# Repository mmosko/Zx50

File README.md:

# Zx50 Distributed Computer

> **A retro-modern, modular computing platform built around the Zilog Z80 microprocessor — featuring paged virtual
memory, high-speed Shadow DMA, and FPGA coprocessing.**

---

## 1. Welcome to the Zx50

The **Zx50** is a custom, modular computing architecture that marries the classic 8-bit computing ethos of the
late-1970s and 1980s with modern high-speed digital engineering.

At the heart of the system is the **Zilog Z80** microprocessor (inducted into
the [IEEE Spectrum Chip Hall of Fame](https://spectrum.ieee.org/chip-hall-of-fame-zilog-z80-microprocessor),
see the official [Zilog Z80 Datasheet](https://www.zilog.com/docs/z80/um0080.pdf)). 
The Zx50 reimagines the Z80 as a modern distributed computing workstation.

### What makes the Zx50 "Retro-Modern"?

* **Bare-Metal Simplicity**: The CPU executes pure, unadulterated Z80 machine code. You can program it in assembly, C,
  or native BASIC just like classic machines.
* **Breaking the 64KB Limit**: A custom hardware Memory Management Unit (MMU) implemented in a CPLD provides 4KB paged
  virtual memory across 1MB+ of physical SRAM.
* **Dual-Bus Highway**: In addition to the standard Z80 bus, a dedicated **40 MHz Shadow DMA Bus** streams data (network
  packets, disk blocks, and peer-to-peer memory transfers) in the background without halting the Z80.
* **Hardware Acceleration**: A modern FPGA coprocessor offloads 32-bit and 64-bit floating-point math, emulating the
  vintage AMD Am9511 APU with single-cycle lookups.
* **Deep Visibility**: Built-in microcontroller instrumentation (RP2040 and Microchip PIC) allows real-time bus
  snooping, cycle-by-cycle single stepping, and telemetry via an active front panel and bus probe.

---

## 2. Core Silicon & Chip Manifest

The Zx50 blends period-accurate Zilog NMOS/CMOS silicon with modern programmable logic and companion microcontrollers:

| Chip / Component              | Technology          | Primary Role in Zx50                                                                                                                               |
|:------------------------------|:--------------------|:---------------------------------------------------------------------------------------------------------------------------------------------------|
| **Zilog Z84C0020**            | CMOS CPU            | **Central Processor**: Runs at 8 MHz – 10 MHz with 16-bit addressing and an 8-bit data path.                                                       |
| **Zilog Z84C30**              | CMOS CTC            | **Counter/Timer Circuit**: 4 independent channels generating periodic system ticks and baud rate clocks.                                           |
| **Zilog Z84C40**              | CMOS DART/SIO       | **Dual Serial Controller**: Dual-channel serial communications (Port 0 for USB console, Port 1 for RS-232) supporting IM 2 vectored interrupts.    |
| **Microchip ATF1508**         | 5V CPLD             | **Memory Controller & MMU**: Address Translation Latch (ATL) mapping 64KB logical address space into 16 independent 4KB pages backed by 1MB+ SRAM. |
| **Lattice MachXO2 / MachXO3** | Flash FPGA          | **Math Coprocessor & SmartNIC**: 32-bit/64-bit floating point APU emulation, fast BRAM LUT math, and future LVDS RDMA distributed clustering.      |
| **WIZnet W5300**              | Hardwired TCP/IP    | **10/100 Ethernet Controller**: Memory-mapped window for wire-speed network packet streaming via Z80 `LDIR`/`LDDR` block transfers.                |
| **WCH CH376S**                | Mass Storage IC     | **USB Host & SD Card Controller**: Hardware FAT16/FAT32 file manager mapped into the Z80 I/O space.                                                |
| **Raspberry Pi RP2040**       | Dual ARM Cortex-M0+ | **Instrumentation & Display**: Drives the Front Panel display/switches and coordinates circular trace buffers on the Bus Probe.                    |
| **Microchip PIC18F4620**      | 8-bit MCU           | **Real-Time Bus Interface**: Works alongside the RP2040 on the Bus Probe for cycle sampling, pin toggling, and non-intrusive bus analysis.         |

---

## 3. System Topology & Card Placement

The Zx50 chassis utilizes an 8-slot passive backplane bus.

### Chassis Slot Tour

* **Card 0: Front Panel**: System human interface featuring a 20x4 LCD, step/run switches, bus activity
  LEDs, and an RP2040 controller mapped to I/O port `0x50`.
* **Card 1: CPU, Clock & FPU FPGA**: Houses the 10 MHz Z80 CPU, the Clock Mezzanine (generating system `ZCLK` and
  `MCLK`), and the FPGA floating-point coprocessor.
* **Card 2: Timer + Serial**: Combines the Z80 CTC and Z80 DART with a dedicated 7.3728 MHz baud oscillator, providing
  dual serial channels (FTDI USB and MAX232 RS-232).
* **Card 3: Memory 0 (Boot / Primary)**: Contains the ATF1508 CPLD MMU, 1MB fast 12ns SRAM, 512KB Flash boot ROM (with
  automatic ROM kill-switch upon boot jump), and Shadow Bus DMA interface.
* **Card 4: Memory 1 (Secondary / NUMA)**: Secondary memory card providing an additional 1MB SRAM and participating in
  peer-to-peer Shadow Bus memory transfers.
* **Card 5: NetStorage (Future)**: Dual-purpose network and storage adapter combining W5300 10/100 Ethernet and CH376S
  USB/SD mass storage with direct 40 MHz Shadow DMA support.
* **Card 6: Expansion Slot (Future)**: Dedicated slot for secondary CPU compute tiles, multi-node LVDS RDMA clustering
  (PGAS), or audio/video synthesizers.
* **Card 7: Bus Probe (Rev B)**: Diagnostic and telemetry card featuring CBT3251 high-speed multiplexers for
  non-intrusive bus snooping, an RP2040 trace analyzer, and a color LCD.

---

## 4. The Backplane Bus & Signals

The passive backplane links all cards across a single multi-conductor bus trunk:

| Bus Group          | Width   | Signals        | Description                                                                                                                           |
|:-------------------|:--------|:---------------|:--------------------------------------------------------------------------------------------------------------------------------------|
| **Address**        | 16-bit  | `A[15:0]`      | Primary Z80 address bus. Snooped by memory card MMUs for 4KB page translations.                                                       |
| **Data**           | 8-bit   | `D[7:0]`       | Primary Z80 bidirectional data bus.                                                                                                   |
| **Control**        | 15-bit  | `C[14:0]`      | `~MREQ`, `~IORQ`, `~RD`, `~WR`, `~M1`, `~WAIT`, `~INT`, `~NMI`, `~RESET`, `~BUSRQ`, `~BUSAK`, `~HALT`, `~RFSH`, `IEI`, `IEO`.         |
| **Shadow Data**    | 9-bit   | `SD[8:0]`      | High-speed DMA data bus (8 data bits + 1 parity bit).                                                                                 |
| **Shadow Control** | 6-bit   | `SC[5:0]`      | `~S_EN` (Bus claim), `SRW` (Read/Write), `~SSTB` (Strobe), `~SINC` (Increment), `~S_BUSY` (Target stall), `~S_DONE` (Terminal count). |
| **GPIO**           | 16-bit  | `GPIO[15:0]`   | General purpose high-speed interconnect and node synchronization lines.                                                               |
| **Clocks**         | 2 lines | `ZCLK`, `MCLK` | `ZCLK` (8–10 MHz) and `MCLK` (4x ZCLK = 32–40 MHz).                                                                                   |

### AC Bus Termination

To preserve signal integrity at high frequencies without the continuous DC power draw of passive pull-up resistors, all
signal lines are **AC terminated** at both physical ends of the backplane using RC networks tied to GND.

---

## 5. Synchronized Clock Domains

The Zx50 operates across three harmonic clock domains:

```
+-------------------------------------------------------------+
|  Oscillator (32 MHz - 40 MHz)                               |
+-------------------------------------------------------------+
         |                                           |
         v (divide by 4)                             v (direct)
+-------------------------+                 +-------------------------+
|  ZCLK (8 MHz - 10 MHz)  |                 |  MCLK (32 MHz - 40 MHz) |
|  Z80 CPU, CTC, DART     |                 |  Shadow DMA, MMU Timing |
+-------------------------+                 +-------------------------+
                                                         |
                                                         v (PLL / 3x - 4x)
                                            +-------------------------+
                                            |  FPGA (96 MHz - 160 MHz)|
                                            |  FPU Coprocessor Math   |
                                            +-------------------------+
```

1. **`ZCLK` (8 MHz – 10 MHz)**: The fundamental processor clock driving CPU instruction fetch and peripheral cycles.
2. **`MCLK` (32 MHz – 40 MHz = 4x `ZCLK`)**: The synchronous master clock coordinating high-speed burst DMA and CPLD
   state machines.
3. **`FPGA Clock` (96 MHz – 160 MHz = 3x to 4x `MCLK`)**: Synthesized internally inside FPGA coprocessors for
   single-cycle math and DSP acceleration.

---

## 6. High-Speed Shadow DMA

The **Shadow Bus** runs in parallel with the primary Z80 bus to eliminate I/O bottlenecks:

* **Cycle-Stealing Transfers**: Using fast 12ns SRAM, memory cards can service a DMA burst during intervals when the Z80
  is not accessing memory, avoiding `~BUSRQ`/`~BUSAK` pauses.
* **Direct Peer-to-Peer Streaming**: NetStorage can stream Ethernet packets or USB file blocks directly into memory card
  SRAM at **40 MHz** without routing bytes through CPU registers.
* **Deterministic Handshaking**: Uses hardware-level strobes (`~SSTB`, `~SINC`) with target stall flow control
  (`~S_BUSY`).

---

## 7. Software Ecosystem

* **[`zx50_monitor/`](file:///Users/marc/Documents/z80/Zx50/zx50_monitor)**: The self-hosting OS kernel and monitor.
  Transitions from SST39SF040 Flash ROM to SRAM via a hardware "Phantom Jump", featuring interrupt-driven asynchronous
  I/O and lock-free Single-Producer / Single-Consumer (SPSC) ring buffers.
* **[`msbasic/`](file:///Users/marc/Documents/z80/Zx50/msbasic)**: Microsoft BASIC adapted to run natively with full
  terminal, file, and hardware integration.
* **[`z80pack/`](file:///Users/marc/Documents/z80/Zx50/z80pack)**: Full emulator and development testbed for running and
  testing Zx50 software without physical hardware.

---

## 8. Repository Layout

* [`boards/`](file:///Users/marc/Documents/z80/Zx50/boards): KiCad hardware schematics, PCB layouts, and exported
  netlists.
* [`docs/hardware/`](file:///Users/marc/Documents/z80/Zx50/docs/hardware): Detailed hardware subsystem specifications,
  errata, and pinouts.
* [`firmware/`](file:///Users/marc/Documents/z80/Zx50/firmware): Microcontroller firmware for the RP2040 and Microchip
  PIC.
* [`mmu/`](file:///Users/marc/Documents/z80/Zx50/mmu): Verilog HDL code for the ATF1508 CPLD memory controller.
* [`fpu/`](file:///Users/marc/Documents/z80/Zx50/fpu): Verilog HDL and simulation testbenches for the MachXO FPGA math
  coprocessor.
* [`AGENTS.md`](file:///Users/marc/Documents/z80/Zx50/AGENTS.md): Architecture guidelines, design philosophy, and coding
  standards for AI assistants.

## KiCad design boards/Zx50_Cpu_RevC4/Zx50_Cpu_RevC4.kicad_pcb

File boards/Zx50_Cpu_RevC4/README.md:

# Zx50 CPU Card (Rev C2)

## 1. Overview

This is the primary CPU board for the Zx50 8-slot passive backplane system. It hosts the Z80 microprocessor (running at 5 MHz to 10 MHz) and acts as the master controller for the primary bus.

Revision C2 updates the design with an upgraded **Math and Stack Coprocessor Cluster** mounted on the bottom side beneath the clock mezzanine shield, expanding private coprocessor memory to **32 KB** and introducing a **12 ns high-speed SRAM** to guarantee single-cycle memory operations at 40 MHz.

Crucially, this board coexists with the **Zx50 Shadow Bus** architecture. It features a hardware-level "firewall" that allows a secondary master (like a Pi Pico on the Bus Probe or Front Panel card) to request the bus via `~BUSRQ`. When the Z80 yields (`~BUSAK`), the CPU card instantly severs itself from the backplane, allowing the secondary master to perform high-speed 40 MHz DMA transfers without electrical contention.

---

## 2. Core Architecture & Logic Families

### The CPU

* **Z80 Microprocessor (`U4`):** Zilog `Z84C00xxP` CMOS variant in a 40-pin DIP package (socketed).

### The Transceiver Firewall (`SN74ABT245BN`)

To drive the heavy capacitance of the 8-slot backplane, this board uses four **`SN74ABT245BN`** octal bus transceivers (`U2`, `U3`, `U5`, `U7`) with high-drive capability. A unified BOM of four '245s optimizes PCB trace routing across all 32 backplane lines.

* **Convention:** "A-Ports" face the Z80; "B-Ports" face the Backplane.
* **Address Bus (`U2`, `U3`):** Direction (`DIR`) is hardwired to `+5V` (A $\rightarrow$ B only).
* **Control Bus (`U7`):** Direction (`DIR`) is hardwired to `+5V` (A $\rightarrow$ B only). *(Unused input `A8` is tied to GND via a 10k$\Omega$ resistor `R2` to prevent CMOS floating-gate oscillation)*.
* **Data Bus (`U5`):** Direction (`DIR`) is dynamically controlled by read/acknowledge steering logic (`D_DIR` driven by `U8` / `R8`). This switches the transceiver to an input state (B $\rightarrow$ A) during standard memory/IO reads or Interrupt Acknowledge (`INTA`) cycles.
* **Isolation (`~OE`):** The `~OE` pins of all four transceivers are driven by inverted `~BUSAK` (`/BUSAK` from `U1` pin 4).

### Glue Logic & Bus Coordination

Discrete "Little Logic" and micro-logic ICs handle high-speed signal translation:

* **`74AHC1G14` (`U1` - Schmitt Inverter):** Inverts the Z80's active-low `~BUSAK` signal to drive the active-low `~OE` pins of the transceiver wall.
* **`74AHCT74` (`U9` - Dual D Flip-Flop):** Latches timing states for wait-state generation.
* **`74AHCT132` (`U10` - Quad Schmitt NAND):** Handles pulse shaping and step-logic gating for debugging.
* **`74LVC1G3208` (`U8` - 3-Input OR-AND Combo):** Manages direction and enable logic for auxiliary bus controls.

---

## 3. Hardware Wait-State Generator (`wait_gen`) Subsystem

The board incorporates a dedicated hardware wait-state generator to support single-step debugging and cycle stretching during fast coprocessor or backplane operations:

* **Dual D Flip-Flop (`SN74AHCT74DRG4` / `U9`):** Latches bus cycle transitions relative to `ZCLK` and `~M1`/`~IORQ`/`~MREQ` edges.
* **Quad Schmitt-Trigger NAND (`74AHCT132` / `U10`):** Provides noise-tolerant pulse shaping and single-step gate logic.
* **Open-Drain Output (`2N7002-7-F` N-Channel MOSFET / `Q2`):** Drives the active-low `~WAIT` line without contention, allowing other cards or the CPLD to safely assert `~WAIT`.
* **Modes Supported:**
1. **Single-Step Execution:** Holds `~WAIT` low at $T_2$/$T_3$ until a manual step pulse is received from the Clock Mezzanine (`J3`) or Front Panel (`J4`).
2. **Programmable Cycle Stretching:** Generates accurate 1-cycle hold states for memory or I/O windows.

---

## 4. Integrated Math & Stack Coprocessor Cluster (Bottom Layer)

Mounted entirely on the back side of the board beneath the Clock Mezzanine copper shield, a high-performance CPLD cluster operates on a dedicated private memory bus.

```text
                  +-----------------------------------+
                  |   ATF1508AS CPLD (PLCC-84 / U11)  |
                  |   Dual Clocks: 20MHz MCLK / 5MHz ZCLK|
                  +-----+-----------------------+-----+
                        |                       |
           CA0-CA14     |                       |  CD0-CD7
         Private Address|                       |  Private Data
                        v                       v
            +-----------+-----------------------+-----------+
            |                                               |
            |   +-------------------+   +---------------+   |
            |   | SST39SF040 Flash  |   | IS61C256AL    |   |
            |   | 32KB Active (55ns)|   | 32KB Active   |   |
            |   | PLCC-32 (U13)     |   | SRAM 28-TSOP1 |   |
            |   +---------+---------+   +-------+-------+   |
            |             |                     |           |
            |             |     ~C_OE / ~C_WE   |           |
            |             +----------+----------+           |
            |                        |                      |
            |               ~F_CE <--+--> ~M_CE             |
            +-----------------------------------------------+

```

### 1. Central Controller (`ATF1508ASx-xxJx84` / `U11`)

* **Package:** 128-macrocell CPLD in an 84-pin PLCC surface-mount socket.
* **Dual Clock Architecture:** Driven by both **20/40 MHz `MCLK**` (`GCLK1`, Pin 83) and **5/10 MHz `ZCLK**` (`CLK`, Pin 2) from the clock mezzanine (`J3`). The internal state machine executes at `MCLK` speed, enabling sub-cycle arithmetic and table lookups before the Z80 samples data.
* **Features:** Hardware multiplication (Quarter-Square algorithm), fast division seed generation, 16.16 fixed-point ALU, trigonometric LUT queries, and custom DMA/stack frame acceleration.

### 2. Private Memory Architecture (Zero `~BUSREQ` Contention)

The CPLD manages its own dedicated private address (`CA0`–`CA14`) and data (`CD0`–`CD7`) buses, isolating coprocessor memory operations from the primary Z80 system bus:

* **Expanded Private Address Space (32 KB):** A full 15-bit address bus (`CA0`–`CA14`) provides **32 KB** of addressable private memory. Upper unused address lines (`A15`–`A18`) on the Flash ROM (`U13`) are tied directly to **`GND`** to guarantee static CMOS levels.
* **Private Flash/EEPROM (`SST39SF040` / `U13`):** 32 KB active window (55 ns NOR Flash) in a 32-pin PLCC footprint (`CONN_PLCC-32-AT-SMT_ADM`). Stores non-volatile lookup tables (Quarter-Square $f(n)=\lfloor n^2/4 \rfloor$, sine/cosine maps, logarithmic tables, reciprocal seeds).
* **Private High-Speed SRAM (`IS61C256AL-12TLI` / `U12`):** 32 KB active window (12 ns High-Speed Static RAM) in a 28-pin TSOP-I footprint. Operates as a private scratchpad, hardware stack frame storage, or modifiable shadow RAM.
* **Consolidated Control Busses:** Read enable (`~C_OE`, Pin 45) and write strobe (`~C_WE`, Pin 46) are shared across both memory ICs. Access targeting is handled via dedicated Chip Enable lines (`~M_CE` on Pin 44 for SRAM; `~F_CE` on Pin 68 for Flash).
* **Pull-Up Protection:** `~M_CE` and `~F_CE` lines are fitted with $10\text{ k}\Omega$ pull-up resistors (`R7`, `R10`) to $+5\text{V}$ to keep both memory chips deselected and High-Z during power-up or CPLD JTAG re-programming.

### 3. Private Memory Access Speed Selector (`J8` - `MEM SPD`)

To support both 20 MHz and 40 MHz `MCLK` speeds without requiring CPLD bitstream re-flashing:

* **Header (`J8`):** 2-pin (1x2) 2.54mm pin header connected to CPLD Pin 81 (`I/O/GCLK3`) with a $10\text{ k}\Omega$ pull-up resistor (`R5`) to $+5\text{V}$.
* **Jumper Open (High / Default):** Standard mode.
* **Jumper Shorted to GND (Low):** High-speed 1-cycle pipeline selection.

### 4. JTAG In-System Programming

* **Header (`J7`):** 6-pin (1x6) 2.54mm male header.
* **Pinout:** $+5\text{V}$ (Pin 1), `GND` (Pin 2), `TMS` (Pin 3), `TDO` (Pin 4), `TDI` (Pin 5), `TCLK` (Pin 6). Compatible with Waveshare USB-JTAG converters and OpenOCD.
* **Offline Option:** The PLCC-32 Flash chip can be extracted and programmed offline using a T48 / TL866-3G universal programmer.

---

## 5. Power-On Reset (POR) Subsystem

Handled by a **Microchip `MCP1316MT-46LE/OT**` Supervisor IC (SOT-23-5, `U6`).

* **Boot Delay:** Imposes a ~200 ms delay on power-up to allow bulk capacitors ($100\,\mu\text{F}$ `C9`) to charge and peripheral clock sources/Picos to initialize before releasing `~RESET`.
* **Threshold:** 4.6V trip point for brown-out protection.
* **Open-Drain Output:** Safely drives the shared `~RESET` rail (`Pin 1`).
* **Manual Reset (`SW1`):** Tactile button connected to `~MR` (`Pin 3`) for debounced hardware reset during bench testing.

---

## 6. 6-Layer Stackup & PCB Routing Strategy

Revision C2 uses a **6-layer stackup** to accommodate the high-density coprocessor cluster beneath the top-side clock shield without interfering with front-side copper:

| Layer | Type | Dedicated Function |
| --- | --- | --- |
| **Layer 1 (Top)** | Signal / Plane | Primary Z80 component traces, Clock Mezzanine RF shield copper ground pour |
| **Layer 2 (GND)** | Power Plane | Continuous $GND$ reference plane |
| **Layer 3 (Inner 1)** | Signal | **Private Coprocessor Bus:** `CA0`–`CA14`, `CD0`–`CD7`, and private control lines (`~M_CE`, `~F_CE`, `~C_OE`, `~C_WE`) |
| **Layer 4 (Inner 2)** | Signal | **Z80 Bus Ingest:** Taps `A0`–`A15`, `D0`–`D7`, and control lines from `U4` to the CPLD |
| **Layer 5 (VCC)** | Power Plane | Continuous $+5\text{V}$ power distribution plane |
| **Layer 6 (Bottom)** | Signal / SMT | Bottom-mounted SMT footprints: ATF1508AS PLCC-84 (`U11`), SST39SF040 PLCC-32 (`U13`), IS61C256AL TSOP-I-28 (`U12`) |

---

## 7. Interfaces & Connectors

| Connector | Type | Description |
| --- | --- | --- |
| **`J1` - Backplane** | 80-Pin Edge Connector | Standard Zx50 2.54mm bus interface. |
| **`J2` - Bus Connect / Step Tap** | 2x2 Pin Socket | Tap for `AUX` (Pin 80), `GPIO15`, `~STEP`, and `~RUN` signals. |
| **`J3` - Clock Mezzanine** | 2x5 Socket (2.54mm) | Ingests `MCLK` (20/40 MHz), `CLK` (5/10 MHz ZCLK), and `~STEP` signals. |
| **`J4` - Front Panel** | 2x5 Right-Angle IDC | Interfaces status LEDs (`RUN`, `HALT`), `~RESET`, `~STEP`, and power lines. |
| **`J5` - TP_D_DIR Debug** | 1x2 Header (2.54mm) | Hardware tap for Data Bus Direction monitoring and GND test point. |
| **`J6` - TP_BUSAK Debug** | 1x2 Header (2.54mm) | Hardware tap for `~BUSAK` signal observation. |
| **`J7` - Coprocessor JTAG** | 1x6 Header (2.54mm) | In-System Programming header for the ATF1508AS CPLD (`+5V`, `GND`, `TMS`, `TDO`, `TDI`, `TCLK`). |
| **`J8` - MEM SPD Jumper** | 1x2 Header (2.54mm) | Hardware jumper for private memory access speed selection (`Pin 81` / `R5`). |

---

## 8. Estimated Power Consumption Analysis

Operating at $5\text{V}$, the Rev C2 CPU card draws a typical active current of **~170 mA (~0.85 W)** and a worst-case peak switching current of **~280 mA (~1.40 W)**. The power load is split between the primary Z80 CPU subsystem and the high-speed coprocessor cluster.

### A. Primary CPU & Bus Interface Subsystem

| Component | Part Number | Qty | Typ. Current | Max Current | Notes |
| --- | --- | --- | --- | --- | --- |
| **Z80 CPU (10 MHz)** | `Z84C00xxP` | 1 | 10 mA | 20 mA | CMOS low-power core |
| **Bus Transceivers** | `SN74ABT245BN` | 4 | 15 mA | 40 mA | Drives 8-slot backplane capacitance |
| **Wait-State Logic** | `74AHCT74` / `132` | 2 | 8 mA | 15 mA | Dual D-FF & Schmitt NAND gates |
| **Glue Logic & Supervisor** | `74AHC1Gxx` / `MCP1316` | 5 | 3 mA | 5 mA | SOT-23 micro-logic & reset controller |
| **Status LEDs & Pull-ups** | `PWR`, `HALT` LEDs | 2 | 8 mA | 10 mA | ~$470\Omega$ current limiting |
| **Subtotal (CPU Side)** |  |  | **~44 mA** | **~90 mA** | **~0.22 W Typ / 0.45 W Max** |

### B. Coprocessor Cluster Subsystem (Bottom Layer)

| Component | Part Number | Qty | Typ. Current | Max Current | Notes |
| --- | --- | --- | --- | --- | --- |
| **CPLD (20/40 MHz MCLK)** | `ATF1508ASx-xxJx84` | 1 | 65 mA | 100 mA | Dynamic $I_{CC}$ scales with MCLK frequency |
| **Private SRAM (12 ns)** | `IS61C256AL-12TLI` | 1 | 15 mA | 30 mA | Active read/write state |
| **Private Flash (55 ns)** | `SST39SF040` | 1 | 15 mA | 30 mA | Active table read state |
| **Subtotal (Coprocessor)** |  |  | **~95 mA** | **~160 mA** | **~0.48 W Typ / 0.80 W Max** |

### C. Total Card Power Summary

* **Typical Active Load:** **139 mA – 170 mA** (~0.70 W – 0.85 W @ 5V)
* **Maximum Peak Load:** **250 mA – 280 mA** (~1.25 W – 1.40 W @ 5V)

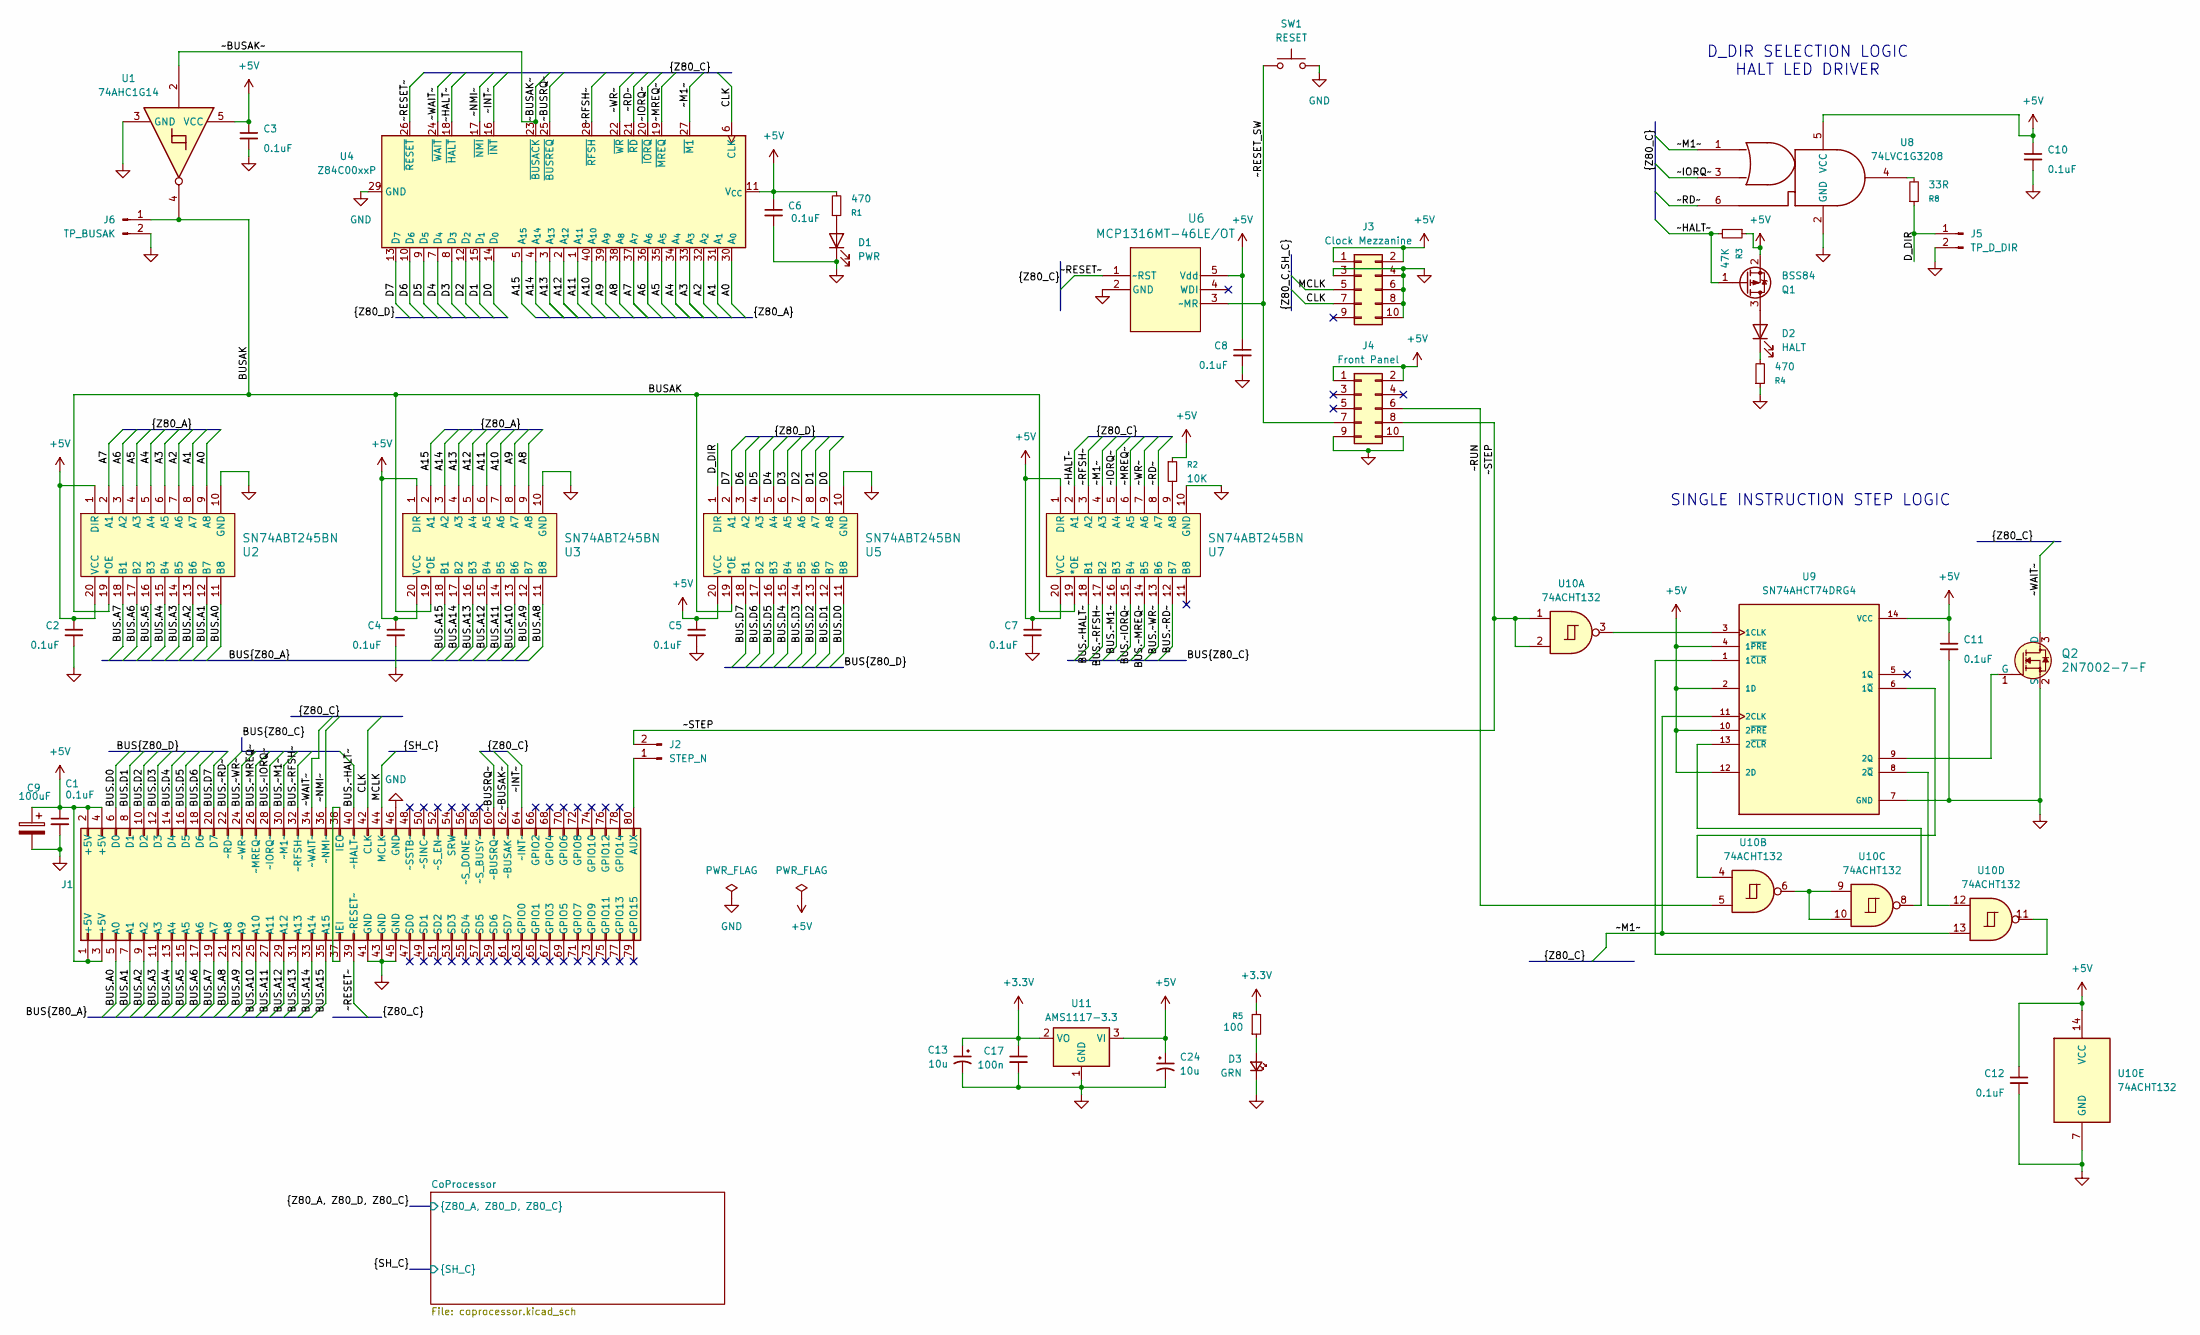
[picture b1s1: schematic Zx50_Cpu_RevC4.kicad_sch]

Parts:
C1, C2, C3, C4, C5, C6, C7, C8, C10, C11, C12: 0.1uF; C_0805_2012Metric_Pad1.18x1.45mm_HandSolder; Mouser_PN 603-CC805KRX7R9BB104; DigiKey_PN 311-1140-1-ND
C9: 100uF; C_Radial_D8.0mm_H7.0mm_P3.50mm
C13: 10u; CP_EIA-3216-10_Kemet-I_HandSolder; MFG PN AVX TAJA106K016RNJ Tantalinium; LCSC C7171
C17: 100n; C_0805_2012Metric_Pad1.18x1.45mm_HandSolder; LCSC C1525
C24: 10u; C_1206_3216Metric; MFG PN AVX Tantalinium; LCSC C7171
D1: PWR; LED_D5.0mm
D2: HALT; LED_D5.0mm
D3: GRN; LED_0805_2012Metric; MFG_PN KT-0805G; LCSC C2297
J1: Zx50_EdgeConnector; PinSocket_2x40_P2.54mm_Vertical_Oval; DigiKey_PN A34273-40-ND
J2: STEP_N; PinHeader_1x02_P2.54mm_Vertical
J3: Clock Mezzanine; PinSocket_2x05_P2.54mm_Horizontal; DigiKey_PN S5558-ND
J4: Front Panel; IDC-Header_2x05_P2.54mm_Horizontal_Edge; DigiKey_PN 732-2098-ND
J5: TP_D_DIR; PinHeader_1x02_P2.54mm_Vertical
J6: TP_BUSAK; PinHeader_1x02_P2.54mm_Vertical
Q1: BSS84; SOT-23
Q2: 2N7002-7-F; SOT-23-3; MPN 2N7002-7-F; Digi-Key_PN 2N7002-FDICT-ND
R1, R4: 470; R_0805_2012Metric_Pad1.20x1.40mm_HandSolder; Mouser_PN 603-RC0805FR-07470RP; DigiKey_PN 311-33.0CRCT-ND
R2: 10K; R_0805_2012Metric_Pad1.20x1.40mm_HandSolder; Mouser_PN 603-RC0805FR-0710KL; DigiKey_PN =
R3: 47K; R_0805_2012Metric_Pad1.20x1.40mm_HandSolder; Mouser_PN 603-RC0805FR-0747KL
R5: 100; R_0805_2012Metric; MFG_PN 0805W8F1000T5E; LCSC C17408
R8: 33R; R_0805_2012Metric_Pad1.20x1.40mm_HandSolder; Mouser_PN 603-RC0805FR-0733RL; DigiKey_PN 311-33.0CRCT-ND
SW1: RESET; SW_PUSH_6mm_H7.3mm; DigiKey_PN SW402-ND
U1: 74AHC1G14; SOT-23-5_HandSoldering; DigiKey_PN 296-1088-1-ND
U2, U3, U5, U7: SN74ABT245BN; SOIC-20W_7.5x12.8mm_P1.27mm
U4: Z84C00xxP; DIP-40_W15.24mm
U6: MCP1316MT-46LE/OT; SOT-23-5_HandSoldering; Digikey_PN MCP1316MT-46LE/OTCT-ND
U8: 74LVC1G3208; SOT-23-6_Handsoldering
U9: SN74AHCT74DRG4; SOIC-14_3.9x8.7mm_P1.27mm; PARTREV O
U10: 74ACHT132; SOIC-14_3.9x8.7mm_P1.27mm
U11: AMS1117-3.3; SOT-223-3_TabPin2; Mouser_PN 926-LM1117MPX3.3NOPB

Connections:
+3.3V: C13.1, C17.1, R5.2, U11.2 (VO); also elsewhere on the board
+5V: C1.1, C2.1, C3.1, C4.1, C5.1, C6.1, C7.1, C8.1, C9.1, C10.1, C11.1, C12.1, C24.1, J1.1 (+5V), J1.2 (+5V), J1.3 (+5V), J1.4 (+5V), J3.1, J3.2, J4.1, J4.2, Q1.2 (S), R1.2, R2.1, R3.1, U1.5 (VCC), U2.1 (DIR), U2.20 (VCC), U3.1 (DIR), U3.20 (VCC), U4.11 (V_{CC}), U5.20 (VCC), U6.5 (Vdd), U7.1 (DIR), U7.20 (VCC), U8.5 (VCC), U9.2 (1D), U9.4 (1~PRE), U9.10 (2~PRE), U9.12 (2D), U9.14 (VCC), U10.14 (VCC), U11.3 (VI); also elsewhere on the board
/A0: U2.9 (A8), U4.30 (A_{0}); also elsewhere on the board
/A1: U2.8 (A7), U4.31 (A_{1}); also elsewhere on the board
/A2: U2.7 (A6), U4.32 (A_{2}); also elsewhere on the board
/A3: U2.6 (A5), U4.33 (A_{3}); also elsewhere on the board
/A4: U2.5 (A4), U4.34 (A_{4}); also elsewhere on the board
/A5: U2.4 (A3), U4.35 (A_{5}); also elsewhere on the board
/A6: U2.3 (A2), U4.36 (A_{6}); also elsewhere on the board
/A7: U2.2 (A1), U4.37 (A_{7}); also elsewhere on the board
/A8: U3.9 (A8), U4.38 (A_{8}); also elsewhere on the board
/A9: U3.8 (A7), U4.39 (A_{9}); also elsewhere on the board
/A10: U3.7 (A6), U4.40 (A_{10}); also elsewhere on the board
/A11: U3.6 (A5), U4.1 (A_{11}); also elsewhere on the board
/A12: U3.5 (A4), U4.2 (A_{12}); also elsewhere on the board
/A13: U3.4 (A3), U4.3 (A_{13}); also elsewhere on the board
/A14: U3.3 (A2), U4.4 (A_{14}); also elsewhere on the board
/A15: U3.2 (A1), U4.5 (A_{15}); also elsewhere on the board
/BUS.A0: J1.5 (A0), U2.11 (B8)
/BUS.A1: J1.7 (A1), U2.12 (B7)
/BUS.A2: J1.9 (A2), U2.13 (B6)
/BUS.A3: J1.11 (A3), U2.14 (B5)
/BUS.A4: J1.13 (A4), U2.15 (B4)
/BUS.A5: J1.15 (A5), U2.16 (B3)
/BUS.A6: J1.17 (A6), U2.17 (B2)
/BUS.A7: J1.19 (A7), U2.18 (B1)
/BUS.A8: J1.21 (A8), U3.11 (B8)
/BUS.A9: J1.23 (A9), U3.12 (B7)
/BUS.A10: J1.25 (A10), U3.13 (B6)
/BUS.A11: J1.27 (A11), U3.14 (B5)
/BUS.A12: J1.29 (A12), U3.15 (B4)
/BUS.A13: J1.31 (A13), U3.16 (B3)
/BUS.A14: J1.33 (A14), U3.17 (B2)
/BUS.A15: J1.35 (A15), U3.18 (B1)
/BUS.D0: J1.6 (D0), U5.11 (B8)
/BUS.D1: J1.8 (D1), U5.12 (B7)
/BUS.D2: J1.10 (D2), U5.13 (B6)
/BUS.D3: J1.12 (D3), U5.14 (B5)
/BUS.D4: J1.14 (D4), U5.15 (B4)
/BUS.D5: J1.16 (D5), U5.16 (B3)
/BUS.D6: J1.18 (D6), U5.17 (B2)
/BUS.D7: J1.20 (D7), U5.18 (B1)
/BUS.~HALT~: J1.40 (~HALT~), U7.18 (B1)
/BUS.~IORQ~: J1.28 (~IORQ~), U7.15 (B4)
/BUS.~M1~: J1.30 (~M1~), U7.16 (B3)
/BUS.~MREQ~: J1.26 (~MREQ~), U7.14 (B5)
/BUS.~RD~: J1.22 (~RD~), U7.12 (B7)
/BUS.~RFSH~: J1.32 (~RFSH~), U7.17 (B2)
/BUS.~WR~: J1.24 (~WR~), U7.13 (B6)
/BUSAK: J6.1, U1.4, U2.19 (*OE), U3.19 (*OE), U5.19 (*OE), U7.19 (*OE)
/CLK: J1.42 (CLK), J3.7, U4.6 (CLK); also elsewhere on the board
/D0: U4.14 (D_{0}), U5.9 (A8); also elsewhere on the board
/D1: U4.15 (D_{1}), U5.8 (A7); also elsewhere on the board
/D2: U4.12 (D_{2}), U5.7 (A6); also elsewhere on the board
/D3: U4.8 (D_{3}), U5.6 (A5); also elsewhere on the board
/D4: U4.7 (D_{4}), U5.5 (A4); also elsewhere on the board
/D5: U4.9 (D_{5}), U5.4 (A3); also elsewhere on the board
/D6: U4.10 (D_{6}), U5.3 (A2); also elsewhere on the board
/D7: U4.13 (D_{7}), U5.2 (A1); also elsewhere on the board
/D_DIR: J5.1, R8.1, U5.1 (DIR)
/MCLK: J1.44 (MCLK), J3.5; also elsewhere on the board
/~BUSAK~: J1.62 (~BUSAK~), U1.2, U4.23 (~BUSACK)
/~BUSRQ~: J1.60 (~BUSRQ~), U4.25 (~BUSREQ)
/~HALT~: Q1.1 (G), R3.2, U4.18 (~HALT), U7.2 (A1)
/~INT~: J1.64 (~INT~), U4.16 (~INT)
/~IORQ~: U4.20 (~IORQ), U7.5 (A4), U8.3; also elsewhere on the board
/~M1~: U4.27 (~M1), U7.4 (A3), U8.1, U9.11 (2CLK), U10.13; also elsewhere on the board
/~MREQ~: U4.19 (~MREQ), U7.6 (A5); also elsewhere on the board
/~NMI~: J1.36 (~NMI~), U4.17 (~NMI)
/~RD~: U4.21 (~RD), U7.8 (A7), U8.6; also elsewhere on the board
/~RESET_SW: J4.7, SW1.1, U6.3 (~MR)
/~RESET~: J1.39 (~RESET~), U4.26 (~RESET), U6.1 (~RST); also elsewhere on the board
/~RFSH~: U4.28 (~RFSH), U7.3 (A2)
/~RUN: J4.6, U10.5
/~STEP: J2.2, J4.8, U10.1, U10.2
/~WAIT~: J1.34 (~WAIT~), Q2.3 (D), U4.24 (~WAIT); also elsewhere on the board
/~WR~: U4.22 (~WR), U7.7 (A6); also elsewhere on the board
GND: C1.2, C2.2, C3.2, C4.2, C5.2, C6.2, C7.2, C8.2, C9.2, C10.2, C11.2, C12.2, C13.2, C17.2, C24.2, D1.1 (K), D3.1 (K), J1.41 (GND), J1.43 (GND), J1.45 (GND), J1.46 (GND), J3.3, J3.4, J3.6, J3.8, J3.10, J4.9, J4.10, J5.2, J6.2, Q2.2 (S), R4.1, SW1.2, U1.3 (GND), U2.10 (GND), U3.10 (GND), U4.29 (GND), U5.10 (GND), U6.2 (GND), U7.10 (GND), U8.2 (GND), U9.7 (GND), U10.7 (GND), U11.1 (GND); also elsewhere on the board
unnamed: D1.2 (A), R1.1
unnamed: D2.2 (A), Q1.3 (D)
unnamed: D2.1 (K), R4.2
unnamed: D3.2 (A), R5.1
unnamed: J1.80 (AUX), J2.1
unnamed: J1.37 (IEI), J1.38 (IEO)
unnamed: Q2.1 (G), U9.9 (2Q)
unnamed: R8.2, U8.4
unnamed: R2.2, U7.9 (A8)
unnamed: U9.3 (1CLK), U10.3
unnamed: U9.1 (1~CLR), U10.11
unnamed: U9.6 (1~Q), U10.4
unnamed: U9.13 (2~CLR), U10.8
unnamed: U9.8 (2~Q), U10.12
unnamed: U10.6, U10.9, U10.10

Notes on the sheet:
D_DIR SELECTION LOGIC HALT LED DRIVER
SINGLE INSTRUCTION STEP LOGIC

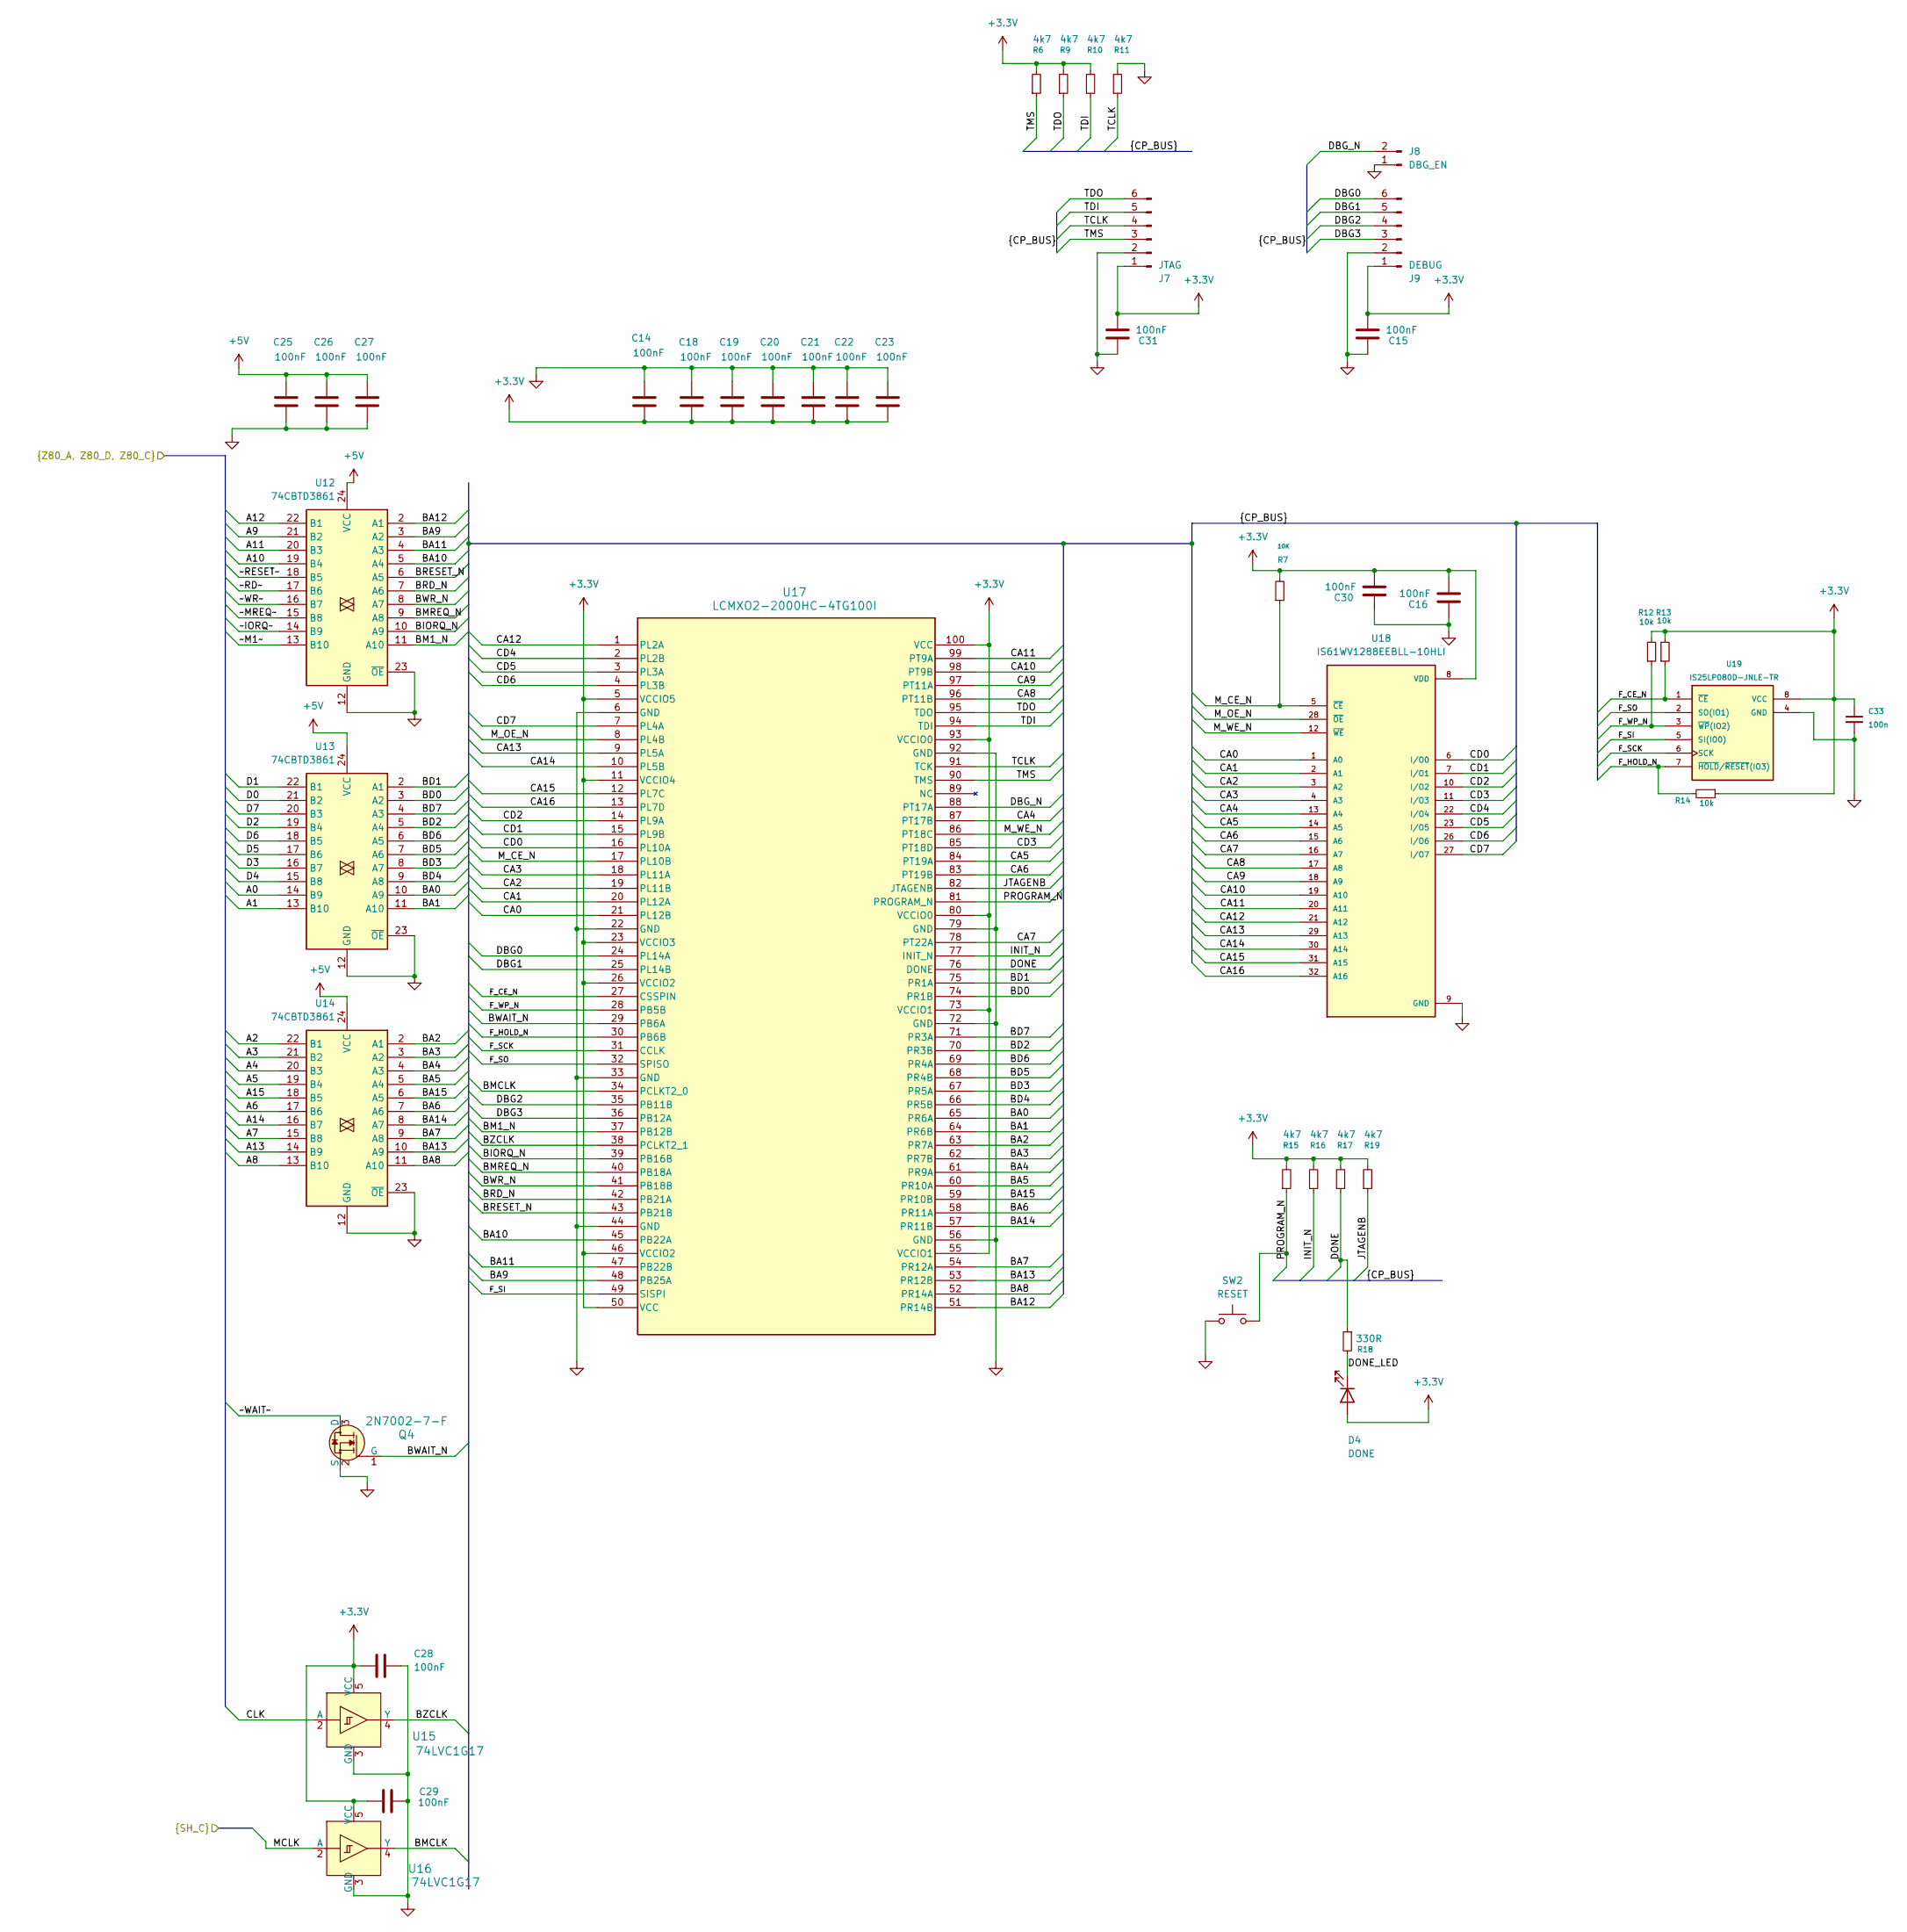
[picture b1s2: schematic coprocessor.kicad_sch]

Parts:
C14, C15, C16, C18, C19, C20, C21, C22, C23, C25, C26, C27, C28, C29, C30, C31: 100nF; C_0805_2012Metric; LCSC C28233
C33: 100n; C_0805_2012Metric; LCSC C49678
D4: DONE; LED_0805_2012Metric; MFG_PN SM0805GCL; LCSC C2297
J7: JTAG; PinHeader_1x06_P2.54mm_Vertical
J8: DBG_EN; PinHeader_1x02_P2.54mm_Vertical
J9: DEBUG; PinHeader_1x06_P2.54mm_Vertical
Q4: 2N7002-7-F; SOT-23-3; MPN 2N7002-7-F; Digi-Key_PN 2N7002-FDICT-ND
R6, R9, R10, R11, R15, R16, R17, R19: 4k7; R_0805_2012Metric; MFG_PN AA0805FR-134K7L; LCSC C17713
R7: 10K; R_0805_2012Metric_Pad1.20x1.40mm_HandSolder; DigiKey_PN =
R12, R13, R14: 10k; R_0805_2012Metric; LCSC C17414
R18: 330R; R_0805_2012Metric_Pad1.20x1.40mm_HandSolder; MFG_PN AC0805JR-13330RL; LCSC C17630
SW2: RESET; SW_SPST_PTS645Sx43SMTR92
U12, U13, U14: 74CBTD3861; DB24; LCSC C11617
U15, U16: 74LVC1G17; SOT-753; MPN SN74LVC1G17DBVR; Digi-Key_PN 296-11933-1-ND
U17: LCMXO2-2000HC-4TG100I; TQFP100_LAT; LCSC C1521620
U18: IS61WV1288EEBLL-10HLI; SOP50P1400X120-32N; PARTREV Rev. B1; LCSC C1349956
U19: IS25LP080D-JNLE-TR; SOIC127P600X88-8N; DigiKey_PN 706-1581-1-ND

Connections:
+3.3V: C14.2, C15.2, C16.2, C18.2, C19.2, C20.2, C21.2, C22.2, C23.2, C28.2, C29.2, C30.2, C31.2, C33.1, D4.2 (A), J7.1, J9.1, R6.2, R7.2, R9.2, R10.2, R12.2, R13.2, R14.1, R15.2, R16.2, R17.2, R19.2, U15.5 (VCC), U16.5 (VCC), U17.5 (VCCIO5), U17.11 (VCCIO4), U17.23 (VCCIO3), U17.26 (VCCIO2), U17.46 (VCCIO2), U17.50 (VCC), U17.55 (VCCIO1), U17.73 (VCCIO1), U17.80 (VCCIO0), U17.93 (VCCIO0), U17.100 (VCC), U18.8 (VDD), U18.24 (VDD), U19.8 (VCC); also elsewhere on the board
+5V: C25.1, C26.1, C27.1, U12.24 (VCC), U13.24 (VCC), U14.24 (VCC); also elsewhere on the board
/A0: U13.14 (B9); also elsewhere on the board
/A1: U13.13 (B10); also elsewhere on the board
/A2: U14.22 (B1); also elsewhere on the board
/A3: U14.21 (B2); also elsewhere on the board
/A4: U14.20 (B3); also elsewhere on the board
/A5: U14.19 (B4); also elsewhere on the board
/A6: U14.17 (B6); also elsewhere on the board
/A7: U14.15 (B8); also elsewhere on the board
/A8: U14.13 (B10); also elsewhere on the board
/A9: U12.21 (B2); also elsewhere on the board
/A10: U12.19 (B4); also elsewhere on the board
/A11: U12.20 (B3); also elsewhere on the board
/A12: U12.22 (B1); also elsewhere on the board
/A13: U14.14 (B9); also elsewhere on the board
/A14: U14.16 (B7); also elsewhere on the board
/A15: U14.18 (B5); also elsewhere on the board
/CLK: U15.2 (A); also elsewhere on the board
/CoProcessor/BA0: U13.10 (A9), U17.65 (PR6A)
/CoProcessor/BA1: U13.11 (A10), U17.64 (PR6B)
/CoProcessor/BA2: U14.2 (A1), U17.63 (PR7A)
/CoProcessor/BA3: U14.3 (A2), U17.62 (PR7B)
/CoProcessor/BA4: U14.4 (A3), U17.61 (PR9A)
/CoProcessor/BA5: U14.5 (A4), U17.60 (PR10A)
/CoProcessor/BA6: U14.7 (A6), U17.58 (PR11A)
/CoProcessor/BA7: U14.9 (A8), U17.54 (PR12A)
/CoProcessor/BA8: U14.11 (A10), U17.52 (PR14A)
/CoProcessor/BA9: U12.3 (A2), U17.48 (PB25A)
/CoProcessor/BA10: U12.5 (A4), U17.45 (PB22A)
/CoProcessor/BA11: U12.4 (A3), U17.47 (PB22B)
/CoProcessor/BA12: U12.2 (A1), U17.51 (PR14B)
/CoProcessor/BA13: U14.10 (A9), U17.53 (PR12B)
/CoProcessor/BA14: U14.8 (A7), U17.57 (PR11B)
/CoProcessor/BA15: U14.6 (A5), U17.59 (PR10B)
/CoProcessor/BD0: U13.3 (A2), U17.74 (PR1B)
/CoProcessor/BD1: U13.2 (A1), U17.75 (PR1A)
/CoProcessor/BD2: U13.5 (A4), U17.70 (PR3B)
/CoProcessor/BD3: U13.8 (A7), U17.67 (PR5A)
/CoProcessor/BD4: U13.9 (A8), U17.66 (PR5B)
/CoProcessor/BD5: U13.7 (A6), U17.68 (PR4B)
/CoProcessor/BD6: U13.6 (A5), U17.69 (PR4A)
/CoProcessor/BD7: U13.4 (A3), U17.71 (PR3A)
/CoProcessor/BIORQ_N: U12.10 (A9), U17.39 (PB16B)
/CoProcessor/BM1_N: U12.11 (A10), U17.37 (PB12B)
/CoProcessor/BMCLK: U16.4 (Y), U17.34 (PCLKT2_0)
/CoProcessor/BMREQ_N: U12.9 (A8), U17.40 (PB18A)
/CoProcessor/BRD_N: U12.7 (A6), U17.42 (PB21A)
/CoProcessor/BRESET_N: U12.6 (A5), U17.43 (PB21B)
/CoProcessor/BWAIT_N: Q4.1 (G), U17.29 (PB6A)
/CoProcessor/BWR_N: U12.8 (A7), U17.41 (PB18B)
/CoProcessor/BZCLK: U15.4 (Y), U17.38 (PCLKT2_1)
/CoProcessor/CA0: U17.21 (PL12B), U18.1 (A0)
/CoProcessor/CA1: U17.20 (PL12A), U18.2 (A1)
/CoProcessor/CA2: U17.19 (PL11B), U18.3 (A2)
/CoProcessor/CA3: U17.18 (PL11A), U18.4 (A3)
/CoProcessor/CA4: U17.87 (PT17B), U18.13 (A4)
/CoProcessor/CA5: U17.84 (PT19A), U18.14 (A5)
/CoProcessor/CA6: U17.83 (PT19B), U18.15 (A6)
/CoProcessor/CA7: U17.78 (PT22A), U18.16 (A7)
/CoProcessor/CA8: U17.96 (PT11B), U18.17 (A8)
/CoProcessor/CA9: U17.97 (PT11A), U18.18 (A9)
/CoProcessor/CA10: U17.98 (PT9B), U18.19 (A10)
/CoProcessor/CA11: U17.99 (PT9A), U18.20 (A11)
/CoProcessor/CA12: U17.1 (PL2A), U18.21 (A12)
/CoProcessor/CA13: U17.9 (PL5A), U18.29 (A13)
/CoProcessor/CA14: U17.10 (PL5B), U18.30 (A14)
/CoProcessor/CA15: U17.12 (PL7C), U18.31 (A15)
/CoProcessor/CA16: U17.13 (PL7D), U18.32 (A16)
/CoProcessor/CD0: U17.16 (PL10A), U18.6 (I/O0)
/CoProcessor/CD1: U17.15 (PL9B), U18.7 (I/O1)
/CoProcessor/CD2: U17.14 (PL9A), U18.10 (I/O2)
/CoProcessor/CD3: U17.85 (PT18D), U18.11 (I/O3)
/CoProcessor/CD4: U17.2 (PL2B), U18.22 (I/O4)
/CoProcessor/CD5: U17.3 (PL3A), U18.23 (I/O5)
/CoProcessor/CD6: U17.4 (PL3B), U18.26 (I/O6)
/CoProcessor/CD7: U17.7 (PL4A), U18.27 (I/O7)
/CoProcessor/DBG0: J9.6, U17.24 (PL14A)
/CoProcessor/DBG1: J9.5, U17.25 (PL14B)
/CoProcessor/DBG2: J9.4, U17.35 (PB11B)
/CoProcessor/DBG3: J9.3, U17.36 (PB12A)
/CoProcessor/DBG_N: J8.2, U17.88 (PT17A)
/CoProcessor/DONE: R17.1, R18.1, U17.76 (DONE)
/CoProcessor/DONE_LED: D4.1 (K), R18.2
/CoProcessor/F_CE_N: R13.1, U17.27 (CSSPIN), U19.1 (~CE)
/CoProcessor/F_HOLD_N: R14.2, U17.30 (PB6B), U19.7 (~HOLD/~RESET(IO3))
/CoProcessor/F_SCK: U17.31 (CCLK), U19.6 (SCK)
/CoProcessor/F_SI: U17.49 (SISPI), U19.5 (SI(IO0))
/CoProcessor/F_SO: U17.32 (SPISO), U19.2 (SO(IO1))
/CoProcessor/F_WP_N: R12.1, U17.28 (PB5B), U19.3 (~WP(IO2))
/CoProcessor/INIT_N: R16.1, U17.77 (INIT_N)
/CoProcessor/JTAGENB: R19.1, U17.82 (JTAGENB)
/CoProcessor/M_CE_N: R7.1, U17.17 (PL10B), U18.5 (~CE)
/CoProcessor/M_OE_N: U17.8 (PL4B), U18.28 (~OE)
/CoProcessor/M_WE_N: U17.86 (PT18C), U18.12 (~WE)
/CoProcessor/PROGRAM_N: R15.1, SW2.2, U17.81 (PROGRAM_N)
/CoProcessor/TCLK: J7.4, R11.1, U17.91 (TCK)
/CoProcessor/TDI: J7.5, R10.1, U17.94 (TDI)
/CoProcessor/TDO: J7.6, R9.1, U17.95 (TDO)
/CoProcessor/TMS: J7.3, R6.1, U17.90 (TMS)
/D0: U13.21 (B2); also elsewhere on the board
/D1: U13.22 (B1); also elsewhere on the board
/D2: U13.19 (B4); also elsewhere on the board
/D3: U13.16 (B7); also elsewhere on the board
/D4: U13.15 (B8); also elsewhere on the board
/D5: U13.17 (B6); also elsewhere on the board
/D6: U13.18 (B5); also elsewhere on the board
/D7: U13.20 (B3); also elsewhere on the board
/MCLK: U16.2 (A); also elsewhere on the board
/~IORQ~: U12.14 (B9); also elsewhere on the board
/~M1~: U12.13 (B10); also elsewhere on the board
/~MREQ~: U12.15 (B8); also elsewhere on the board
/~RD~: U12.17 (B6); also elsewhere on the board
/~RESET~: U12.18 (B5); also elsewhere on the board
/~WAIT~: Q4.3 (D); also elsewhere on the board
/~WR~: U12.16 (B7); also elsewhere on the board
GND: C14.1, C15.1, C16.1, C18.1, C19.1, C20.1, C21.1, C22.1, C23.1, C25.2, C26.2, C27.2, C28.1, C29.1, C30.1, C31.1, C33.2, J7.2, J8.1, J9.2, Q4.2 (S), R11.2, SW2.1, U12.12 (GND), U12.23 (~OE), U13.12 (GND), U13.23 (~OE), U14.12 (GND), U14.23 (~OE), U15.3 (GND), U16.3 (GND), U17.6 (GND), U17.22 (GND), U17.33 (GND), U17.44 (GND), U17.56 (GND), U17.72 (GND), U17.79 (GND), U17.92 (GND), U18.9 (GND), U18.25 (GND), U19.4 (GND); also elsewhere on the board
